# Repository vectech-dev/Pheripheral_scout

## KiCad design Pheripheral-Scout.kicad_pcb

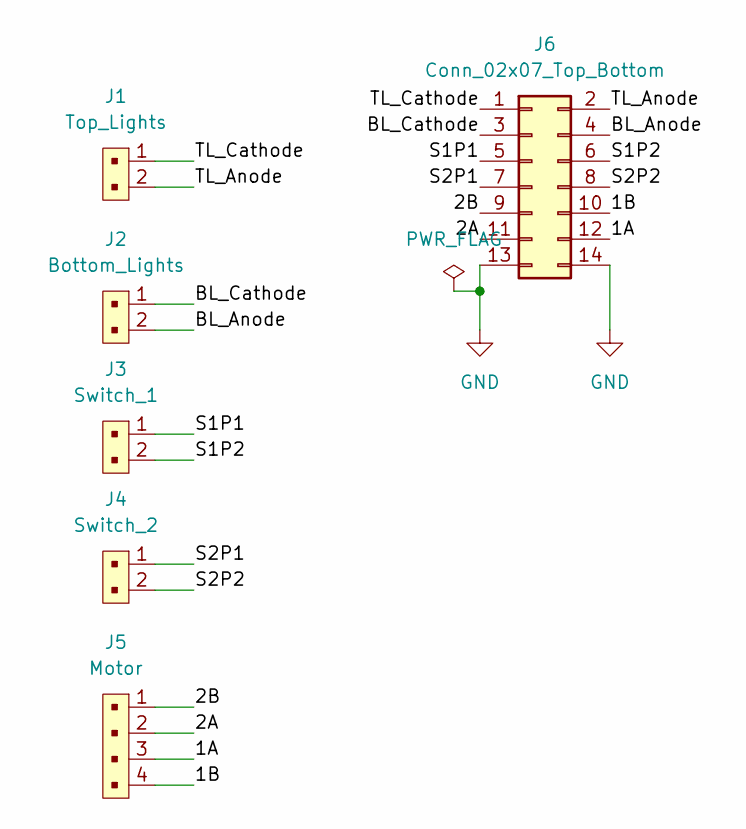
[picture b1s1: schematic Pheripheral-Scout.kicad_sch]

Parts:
J1: Top_Lights; PinHeader_1x2_P2mm_Drill1mm; MPN B2B-XH-A(LF)(SN); Digi-Key_PN 455-2247-ND
J2: Bottom_Lights; PinHeader_1x2_P2mm_Drill1mm; MPN B2B-XH-A(LF)(SN); Digi-Key_PN 455-2247-ND
J3: Switch_1; PinHeader_1x2_P2mm_Drill1mm; MPN B2B-XH-A(LF)(SN); Digi-Key_PN 455-2247-ND
J4: Switch_2; PinHeader_1x2_P2mm_Drill1mm; MPN B2B-XH-A(LF)(SN); Digi-Key_PN 455-2247-ND
J5: Motor; PinHeader_1x4_P2mm_Drill1mm; MPN B4B-XH-A(LF)(SN); Digi-Key_PN 455-2249-ND
J6: Conn_02x07_Top_Bottom; IDC-Header_2x07_P2.54mm_Vertical

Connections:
/1A: J5.3, J6.12
/1B: J5.4, J6.10
/2A: J5.2, J6.11
/2B: J5.1, J6.9
/BL_Anode: J2.2, J6.4
/BL_Cathode: J2.1, J6.3
/S1P1: J3.1, J6.5
/S1P2: J3.2, J6.6
/S2P1: J4.1, J6.7
/S2P2: J4.2, J6.8
/TL_Anode: J1.2, J6.2
/TL_Cathode: J1.1, J6.1
GND: J6.13, J6.14

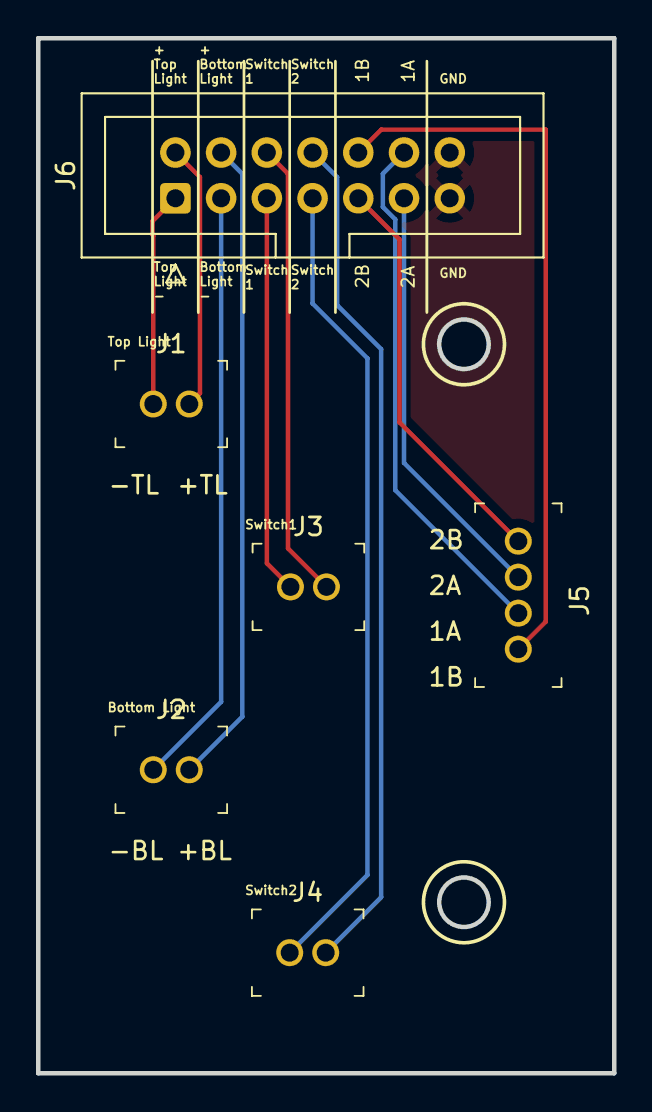
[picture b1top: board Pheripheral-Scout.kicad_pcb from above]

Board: 2 copper layers, 32.0 x 57.5 mm, 6 parts (0 on the bottom side), 13 nets.

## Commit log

2024-07-15 first
2024-07-16 Alpha Prototype ready
2024-08-28 Updated BOM
